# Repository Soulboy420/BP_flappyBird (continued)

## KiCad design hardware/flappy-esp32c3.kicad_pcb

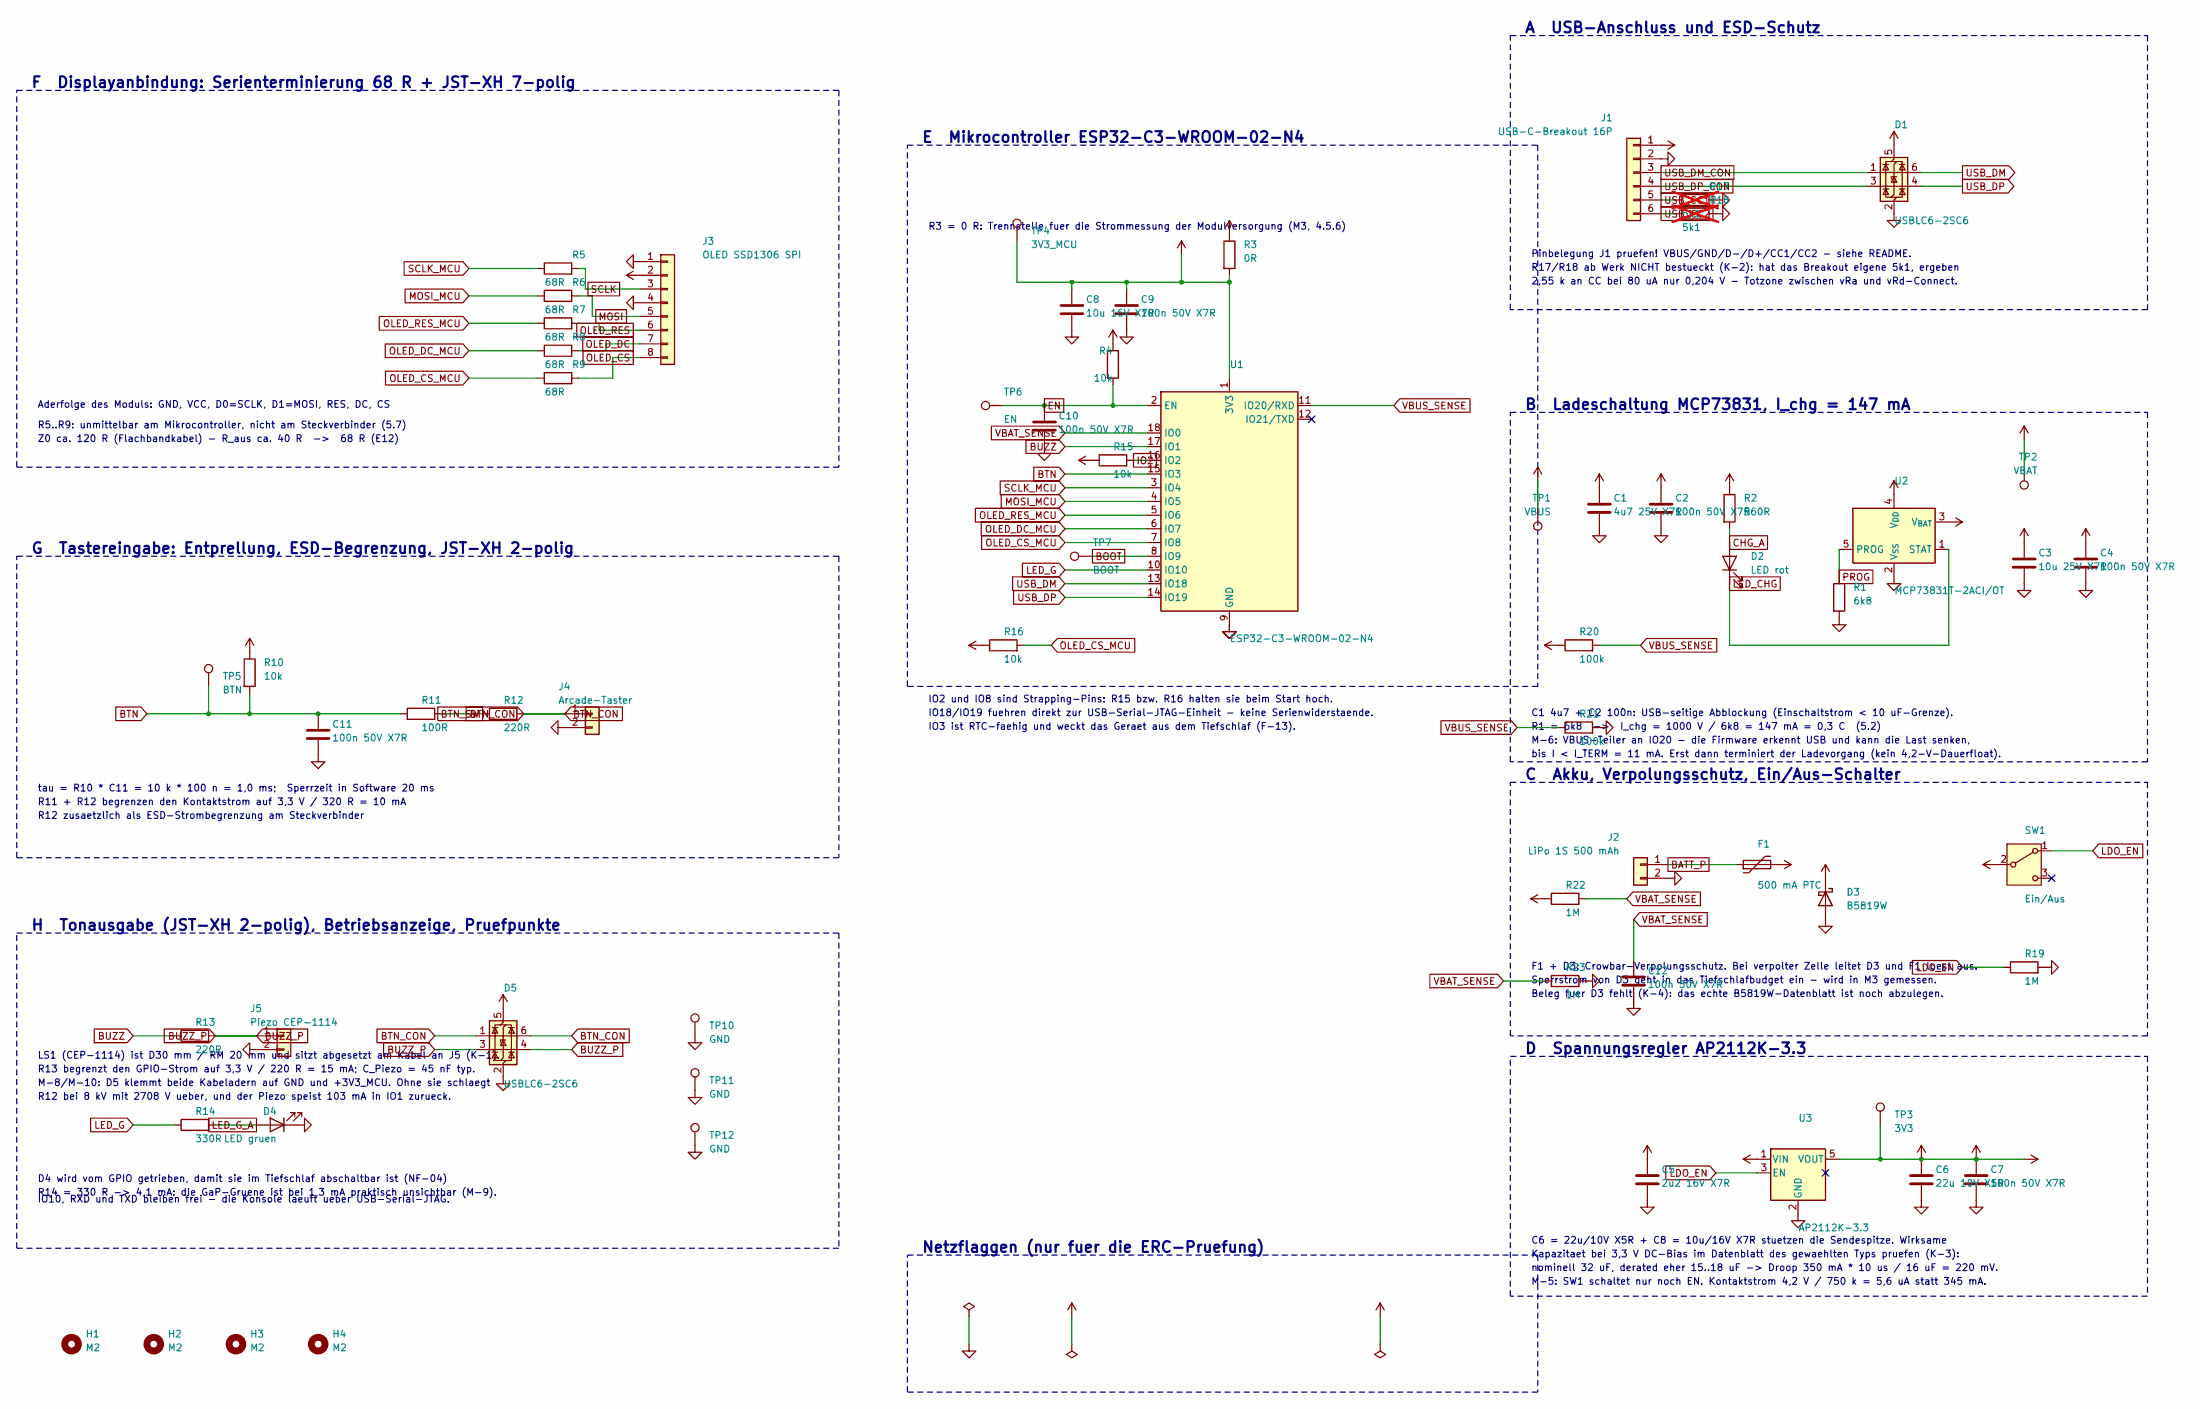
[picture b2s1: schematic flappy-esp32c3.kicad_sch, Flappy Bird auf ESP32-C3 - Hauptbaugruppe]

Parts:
C1: 4u7 25V X7R; C_0805_2012Metric_Pad1.18x1.45mm_HandSolder
C2, C4, C7, C9, C10, C11, C12: 100n 50V X7R; C_0805_2012Metric_Pad1.18x1.45mm_HandSolder
C3: 10u 25V X7R; C_0805_2012Metric_Pad1.18x1.45mm_HandSolder
C5: 2u2 16V X7R; C_0805_2012Metric_Pad1.18x1.45mm_HandSolder
C6: 22u 10V X5R; C_0805_2012Metric_Pad1.18x1.45mm_HandSolder
C8: 10u 16V X7R; C_0805_2012Metric_Pad1.18x1.45mm_HandSolder
D1, D5: USBLC6-2SC6; SOT-23-6_Handsoldering
D2: LED rot; LED_0805_2012Metric_Pad1.15x1.40mm_HandSolder
D3: B5819W; D_SOD-123
D4: LED gruen; LED_0805_2012Metric_Pad1.15x1.40mm_HandSolder
F1: 500 mA PTC; R_0805_2012Metric_Pad1.20x1.40mm_HandSolder
H1, H2, H3, H4: M2; MountingHole_2.2mm_M2
J1: USB-C-Breakout 16P; PinHeader_1x06_P2.54mm_Vertical
J2: LiPo 1S 500 mAh; JST_PH_B2B-PH-K_1x02_P2.00mm_Vertical
J3: OLED SSD1306 SPI; JST_XH_B8B-XH-A_1x08_P2.50mm_Vertical
J4: Arcade-Taster; JST_XH_B2B-XH-A_1x02_P2.50mm_Vertical
J5: Piezo CEP-1114; JST_XH_B2B-XH-A_1x02_P2.50mm_Vertical
R1: 6k8; R_0805_2012Metric_Pad1.20x1.40mm_HandSolder
R2: 560R; R_0805_2012Metric_Pad1.20x1.40mm_HandSolder
R3: 0R; R_0805_2012Metric_Pad1.20x1.40mm_HandSolder
R4, R10, R15, R16: 10k; R_0805_2012Metric_Pad1.20x1.40mm_HandSolder
R5, R6, R7, R8, R9: 68R; R_0805_2012Metric_Pad1.20x1.40mm_HandSolder
R11: 100R; R_0805_2012Metric_Pad1.20x1.40mm_HandSolder
R12, R13: 220R; R_0805_2012Metric_Pad1.20x1.40mm_HandSolder
R14: 330R; R_0805_2012Metric_Pad1.20x1.40mm_HandSolder
R17, R18: 5k1; R_0805_2012Metric_Pad1.20x1.40mm_HandSolder; not fitted
R19, R22, R23: 1M; R_0805_2012Metric_Pad1.20x1.40mm_HandSolder
R20, R21: 100k; R_0805_2012Metric_Pad1.20x1.40mm_HandSolder
SW1: Ein/Aus; SW_Slide_SPDT_Straight_CK_OS102011MS2Q
TP1: VBUS; TestPoint_Pad_D1.5mm
TP2: VBAT; TestPoint_Pad_D1.5mm
TP3: 3V3; TestPoint_Pad_D1.5mm
TP4: 3V3_MCU; TestPoint_Pad_D1.5mm
TP5: BTN; TestPoint_Pad_D1.5mm
TP6: EN; TestPoint_Pad_D1.5mm
TP7: BOOT; TestPoint_Pad_D1.5mm
TP10, TP11, TP12: GND; TestPoint_Pad_D1.5mm
U1: ESP32-C3-WROOM-02-N4; ESP32-C3-WROOM-02_HandSolder
U2: MCP73831T-2ACI/OT; SOT-23-5_HandSoldering
U3: AP2112K-3.3; SOT-23-5_HandSoldering

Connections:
+3V3: C6.1, C7.1, J3.2, R3.1, TP3.1, U3.5 (VOUT)
+3V3_MCU: C8.1, C9.1, D5.5 (VBUS), R3.2, R4.2, R10.1, R15.1, R16.1, TP4.1, U1.1 (3V3)
BATT_P: F1.1, J2.1
BOOT: TP7.1, U1.8 (IO9)
BTN: C11.1, R10.2, R11.1, TP5.1, U1.15 (IO3)
BTN_CON: D5.1 (I/O1), D5.6 (I/O1), J4.1, R12.2
BTN_SW: R11.2, R12.1
BUZZ: R13.1, U1.17 (IO1)
BUZZ_P: D5.3 (I/O2), D5.4 (I/O2), J5.1, R13.2
CHG_A: D2.2 (A), R2.2
EN: C10.1, R4.1, TP6.1, U1.2 (EN)
GND: C1.2, C2.2, C3.2, C4.2, C5.2, C6.2, C7.2, C8.2, C9.2, C10.2, C11.2, C12.2, D1.2 (GND), D3.2 (A), D4.1 (K), D5.2 (GND), J1.2, J2.2, J3.1, J3.4, J4.2, J5.2, R1.2, R17.2, R18.2, R19.2, R21.2, R23.2, TP10.1, TP11.1, TP12.1, U1.9 (GND), U1.19 (GND), U2.2 (V_{SS}), U3.2 (GND)
IO2: R15.2, U1.16 (IO2)
LDO_EN: R19.1, SW1.1 (A), U3.3 (EN)
LED_CHG: D2.1 (K), U2.1 (STAT)
LED_G: R14.1, U1.10 (IO10)
LED_G_A: D4.2 (A), R14.2
MOSI: J3.5, R6.2
MOSI_MCU: R6.1, U1.4 (IO5)
OLED_CS: J3.8, R9.2
OLED_CS_MCU: R9.1, R16.2, U1.7 (IO8)
OLED_DC: J3.7, R8.2
OLED_DC_MCU: R8.1, U1.6 (IO7)
OLED_RES: J3.6, R7.2
OLED_RES_MCU: R7.1, U1.5 (IO6)
PROG: R1.1, U2.5 (PROG)
SCLK: J3.3, R5.2
SCLK_MCU: R5.1, U1.3 (IO4)
USB_CC1: J1.5, R17.1
USB_CC2: J1.6, R18.1
USB_DM: D1.6 (I/O1), U1.13 (IO18)
USB_DM_CON: D1.1 (I/O1), J1.3
USB_DP: D1.4 (I/O2), U1.14 (IO19)
USB_DP_CON: D1.3 (I/O2), J1.4
VBAT: C3.1, C4.1, C5.1, D3.1 (K), F1.2, R22.1, SW1.2 (B), TP2.1, U2.3 (V_{BAT}), U3.1 (VIN)
VBAT_SENSE: C12.1, R22.2, R23.1, U1.18 (IO0)
VBUS: C1.1, C2.1, D1.5 (VBUS), J1.1, R2.1, R20.1, TP1.1, U2.4 (V_{DD})
VBUS_SENSE: R20.2, R21.1, U1.11 (IO20/RXD)

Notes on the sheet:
F Displayanbindung: Serienterminierung 68 R + JST-XH 7-polig
G Tastereingabe: Entprellung, ESD-Begrenzung, JST-XH 2-polig
H Tonausgabe (JST-XH 2-polig), Betriebsanzeige, Pruefpunkte
E Mikrocontroller ESP32-C3-WROOM-02-N4
Netzflaggen (nur fuer die ERC-Pruefung)
A USB-Anschluss und ESD-Schutz
B Ladeschaltung MCP73831, I_chg = 147 mA
C Akku, Verpolungsschutz, Ein/Aus-Schalter
D Spannungsregler AP2112K-3.3
R5..R9: unmittelbar am Mikrocontroller, nicht am Steckverbinder (5.7)
Z0 ca. 120 R (Flachbandkabel) - R_aus ca. 40 R -> 68 R (E12)
Aderfolge des Moduls: GND, VCC, D0=SCLK, D1=MOSI, RES, DC, CS
tau = R10 * C11 = 10 k * 100 n = 1,0 ms; Sperrzeit in Software 20 ms
R11 + R12 begrenzen den Kontaktstrom auf 3,3 V / 320 R = 10 mA
R12 zusaetzlich als ESD-Strombegrenzung am Steckverbinder
LS1 (CEP-1114) ist D30 mm / RM 20 mm und sitzt abgesetzt am Kabel an J5 (K-1).
M-8/M-10: D5 klemmt beide Kabeladern auf GND und +3V3_MCU. Ohne sie schlaegt
R12 bei 8 kV mit 2708 V ueber, und der Piezo speist 103 mA in IO1 zurueck.
R13 begrenzt den GPIO-Strom auf 3,3 V / 220 R = 15 mA; C_Piezo = 45 nF typ.
D4 wird vom GPIO getrieben, damit sie im Tiefschlaf abschaltbar ist (NF-04)
R14 = 330 R -> 4,1 mA: die GaP-Gruene ist bei 1,3 mA praktisch unsichtbar (M-9).
IO10, RXD und TXD bleiben frei - die Konsole laeuft ueber USB-Serial-JTAG.
R3 = 0 R: Trennstelle fuer die Strommessung der Modulversorgung (M3, 4.5.6)
IO2 und IO8 sind Strapping-Pins: R15 bzw. R16 halten sie beim Start hoch.
IO18/IO19 fuehren direkt zur USB-Serial-JTAG-Einheit - keine Serienwiderstaende.
IO3 ist RTC-faehig und weckt das Geraet aus dem Tiefschlaf (F-13).
Pinbelegung J1 pruefen! VBUS/GND/D-/D+/CC1/CC2 - siehe README.
R17/R18 ab Werk NICHT bestueckt (K-2): hat das Breakout eigene 5k1, ergeben
2,55 k an CC bei 80 uA nur 0,204 V - Totzone zwischen vRa und vRd-Connect.
C1 4u7 + C2 100n: USB-seitige Abblockung (Einschaltstrom < 10 uF-Grenze).
R1 = 6k8 -> I_chg = 1000 V / 6k8 = 147 mA = 0,3 C (5.2)
M-6: VBUS-Teiler an IO20 - die Firmware erkennt USB und kann die Last senken,
bis I < I_TERM = 11 mA. Erst dann terminiert der Ladevorgang (kein 4,2-V-Dauerfloat).
F1 + D3: Crowbar-Verpolungsschutz. Bei verpolter Zelle leitet D3 und F1 loest aus.
Sperrstrom von D3 geht in das Tiefschlafbudget ein - wird in M3 gemessen.
Beleg fuer D3 fehlt (K-4): das echte B5819W-Datenblatt ist noch abzulegen.
C6 = 22u/10V X5R + C8 = 10u/16V X7R stuetzen die Sendespitze. Wirksame
Kapazitaet bei 3,3 V DC-Bias im Datenblatt des gewaehlten Typs pruefen (K-3):
nominell 32 uF, derated eher 15..18 uF -> Droop 350 mA * 10 us / 16 uF = 220 mV.
M-5: SW1 schaltet nur noch EN. Kontaktstrom 4,2 V / 750 k = 5,6 uA statt 345 mA.

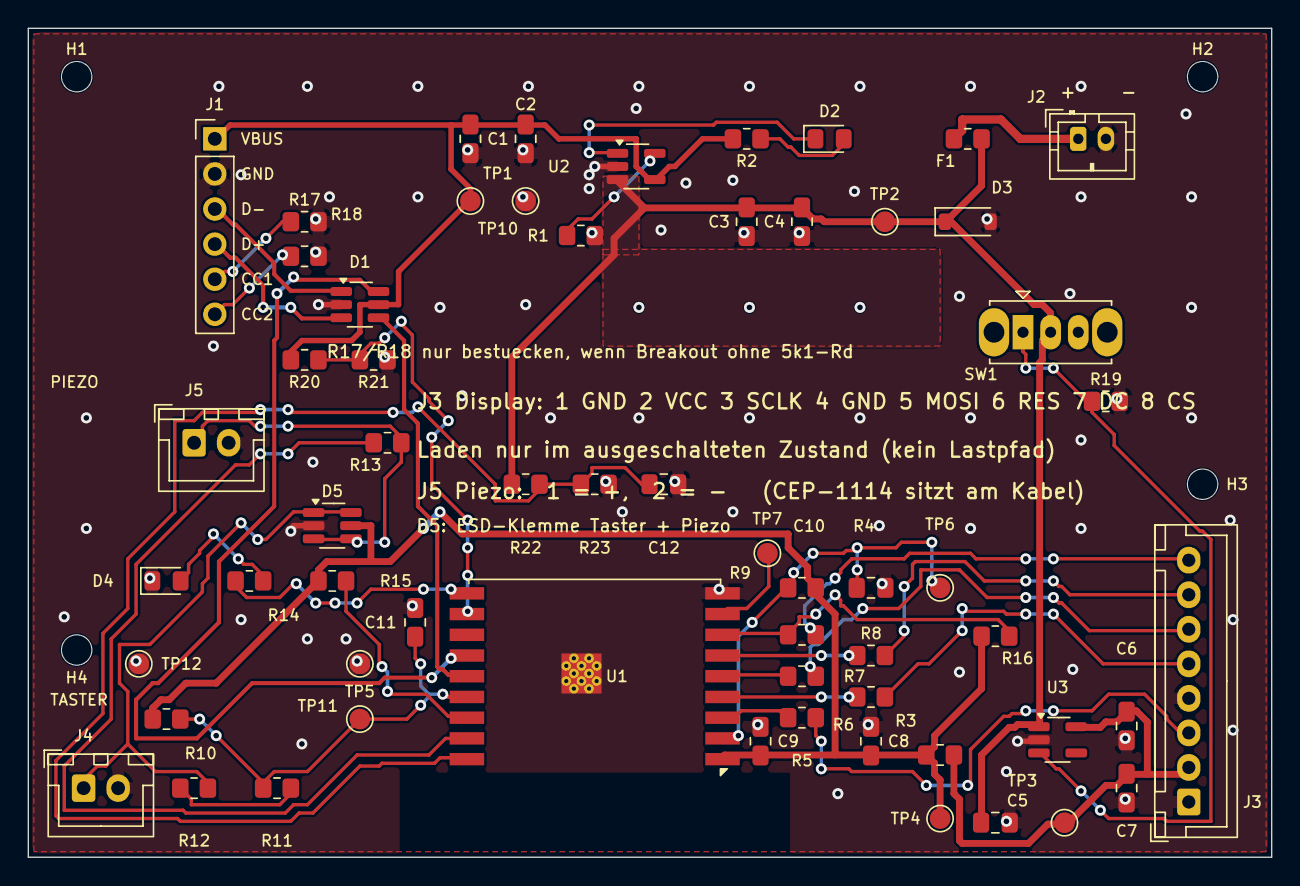
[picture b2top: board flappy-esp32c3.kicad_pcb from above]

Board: 2 copper layers, 90.0 x 60.0 mm, 64 parts (0 on the bottom side), 38 nets.

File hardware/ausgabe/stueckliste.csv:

"Referenz";"Wert";"Footprint";"Anzahl";"Beschreibung"
"C1";"4u7 25V X7R";"Capacitor_SMD:C_0805_2012Metric_Pad1.18x1.45mm_HandSolder";"1";"Eingangskondensator VBUS (VBUS 5,25 V -> >= 2x Derating)"
"C2,C4,C7,C9-C11";"100n 50V X7R";"Capacitor_SMD:C_0805_2012Metric_Pad1.18x1.45mm_HandSolder";"6";"Entprellkondensator Taster,HF-Abblockung 3V3,HF-Abblockung VBAT,HF-Abblockung VBUS,HF-Abblockung am Modul,Reset-Zeitkonstante EN"
"C3";"10u 25V X7R";"Capacitor_SMD:C_0805_2012Metric_Pad1.18x1.45mm_HandSolder";"1";"Ausgangskondensator Laderegler: >= 4,7 uF wirksam bei 4,2 V"
"C5";"2u2 16V X7R";"Capacitor_SMD:C_0805_2012Metric_Pad1.18x1.45mm_HandSolder";"1";"Eingangskondensator LDO: >= 1 uF wirksam bei 4,2 V"
"C6";"22u 10V X5R";"Capacitor_SMD:C_0805_2012Metric_Pad1.18x1.45mm_HandSolder";"1";"Ausgangskondensator LDO (5.4)"
"C8";"10u 16V X7R";"Capacitor_SMD:C_0805_2012Metric_Pad1.18x1.45mm_HandSolder";"1";"Stuetzkondensator am Modul (5.4)"
"D1";"USBLC6-2SC6";"Package_TO_SOT_SMD:SOT-23-6_Handsoldering";"1";"ESD-Schutzarray USB"
"D2";"LED rot";"LED_SMD:LED_0805_2012Metric_Pad1.15x1.40mm_HandSolder";"1";"Ladeanzeige"
"D3";"B5819W";"Diode_SMD:D_SOD-123";"1";"Verpolungsschutz (Crowbar)"
"D4";"LED gruen";"LED_SMD:LED_0805_2012Metric_Pad1.15x1.40mm_HandSolder";"1";"Betriebsanzeige, GPIO-gesteuert"
"F1";"500 mA PTC";"Resistor_SMD:R_0805_2012Metric_Pad1.20x1.40mm_HandSolder";"1";"Rueckstellsicherung Akkupfad"
"J1";"USB-C-Breakout 16P";"Connector_PinHeader_2.54mm:PinHeader_1x06_P2.54mm_Vertical";"1";"VBUS/GND/D-/D+/CC1/CC2"
"J2";"LiPo 1S 500 mAh";"Connector_JST:JST_PH_B2B-PH-K_1x02_P2.00mm_Vertical";"1";"Akkubuchse JST-PH"
"J3";"OLED SSD1306 SPI";"Connector_JST:JST_XH_B7B-XH-A_1x07_P2.50mm_Vertical";"1";"Displaykabel JST-XH 7-polig"
"J4";"Arcade-Taster";"Connector_JST:JST_XH_B2B-XH-A_1x02_P2.50mm_Vertical";"1";"Tasterkabel JST-XH 2-polig"
"J5";"Piezo CEP-1114";"Connector_JST:JST_XH_B2B-XH-A_1x02_P2.50mm_Vertical";"1";"Buzzerkabel JST-XH 2-polig"
"R1";"6k8";"Resistor_SMD:R_0805_2012Metric_Pad1.20x1.40mm_HandSolder";"1";"R_prog -> I_chg = 147 mA"
"R2";"560R";"Resistor_SMD:R_0805_2012Metric_Pad1.20x1.40mm_HandSolder";"1";"Vorwiderstand Lade-LED: (5,0-1,8-0,4)/560 = 5,0 mA"
"R3";"0R";"Resistor_SMD:R_0805_2012Metric_Pad1.20x1.40mm_HandSolder";"1";"Trennstelle Strommessung Modul (M3)"
"R4,R10,R15,R16";"10k";"Resistor_SMD:R_0805_2012Metric_Pad1.20x1.40mm_HandSolder";"4";"Pull-up EN,Pull-up Strapping IO2,Pull-up Strapping IO8,Pull-up Taster, tau = 1,0 ms"
"R5-R9";"68R";"Resistor_SMD:R_0805_2012Metric_Pad1.20x1.40mm_HandSolder";"5";"Serienterminierung CS,Serienterminierung DC,Serienterminierung MOSI,Serienterminierung RES,Serienterminierung SCLK"
"R11";"100R";"Resistor_SMD:R_0805_2012Metric_Pad1.20x1.40mm_HandSolder";"1";"Entladestrombegrenzung Tasterkontakt"
"R12,R13";"220R";"Resistor_SMD:R_0805_2012Metric_Pad1.20x1.40mm_HandSolder";"2";"ESD-Strombegrenzung am Steckverbinder,Strombegrenzung Piezo: 3,3 V / 220 R = 15 mA < 28 mA (I_OL)"
"R14";"330R";"Resistor_SMD:R_0805_2012Metric_Pad1.20x1.40mm_HandSolder";"1";"Vorwiderstand Betriebs-LED: (3,3-1,95)/330 = 4,1 mA"
"R17,R18";"5k1";"Resistor_SMD:R_0805_2012Metric_Pad1.20x1.40mm_HandSolder";"2";"NICHT BESTUECKEN (DNP) - Pull-down CC1, nur wenn Breakout ohne Rd,NICHT BESTUECKEN (DNP) - Pull-down CC2, nur wenn Breakout ohne Rd"
"SW1";"Ein/Aus";"Button_Switch_THT:SW_Slide_SPDT_Straight_CK_OS102011MS2Q";"1";"Schiebeschalter SPDT"
"U1";"ESP32-C3-WROOM-02-N4";"flappy:ESP32-C3-WROOM-02_HandSolder";"1";"Funkmodul, RISC-V, WLAN/BLE, USB-Serial-JTAG"
"U2";"MCP73831T-2ACI/OT";"Package_TO_SOT_SMD:SOT-23-5_HandSoldering";"1";"LiPo-Laderegler 4,20 V, 10 % Vorkond., 7,5 % Abschaltung"
"U3";"AP2112K-3.3";"Package_TO_SOT_SMD:SOT-23-5_HandSoldering";"1";"LDO 3,3 V / 600 mA"

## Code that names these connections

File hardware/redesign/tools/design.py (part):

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{1:'3V3',2:'GND',3:'OLED_EN',4:None,5:'OLED_DISCHARGE',6:'OLED_3V3'},(61,32,0),3,'Texas Instruments','TPS22919DCKR','SC70-6')
add('J1','Connector:USB_C_Receptacle_USB2.0_16P','USB4105-GF-A','Connector_USB:USB_C_Receptacle_GCT_USB4105-xx-A_16P_TopMnt_Horizontal',
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add('J2','Connector_Generic:Conn_01x02','BAT 1S protected',PH2,{1:'PACK_POS',2:'GND'},(6,31,270),1,'JST','B2B-PH-K-S(LF)(SN)','PH 2mm THT',note='Pin 1 POSITIVE; independently verify cable, protected 4.2V Li-ion pack only')
add('J3','Connector_Generic:Conn_01x08','OLED 8 pin','Connector_JST:JST_XH_B8B-XH-A_1x08_P2.50mm_Vertical',
{1:'GND',2:'OLED_3V3',3:'SCK',4:'GND',5:'MOSI',6:'OLED_RESET_N',7:'OLED_DC',8:'OLED_CS_N'},(63,54,180),3,'JST','B8B-XH-A(LF)(SN)','XH 2.5mm THT',note='Board pin sequence is fixed; real OLED cable is a release gate')
add('J4','Connector_Generic:Conn_01x02','BUTTON dry contact',XH2,{1:'BUTTON_EXT',2:'GND'},(77,53,0),4,'JST','B2B-XH-A(LF)(SN)','XH 2.5mm THT')
add('J5','Connector_Generic:Conn_01x02','PASSIVE PIEZO',XH2,{1:'PIEZO_P',2:'PIEZO_N'},(26,54,0),4,'JST','B2B-XH-A(LF)(SN)','XH 2.5mm THT',note='Floating passive piezo only; no magnetic buzzer; two-wire isolated from chassis')
add('J6','Connector_Generic:Conn_01x02','PACK NTC 10k',PH2,{1:'NTC_EXT',2:'GND'},(6,40,270),1,'JST','B2B-PH-K-S(LF)(SN)','PH 2mm THT',note='External Semitec 103AT-2 attached to pack; open cable inhibits charging')
add('SW1','Switch:SW_SPDT','RUN / OFF','Button_Switch_THT:SW_Slide_SPDT_Straight_CK_OS102011MS2Q',
{1:'VSYS',2:'RUN_EN',3:'GND'},(5,18,270),1,'C&K (Littelfuse)','OS102011MS2QN1','SPDT 2mm THT',note='Only enable current; verify exact switch drawing and cable-free mechanical fit')
# USB: one Rd per CC, upstream fast fuse, high-energy VBUS TVS; charging input is 28V tolerant.
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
